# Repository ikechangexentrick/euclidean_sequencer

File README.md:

# euclidean_sequencer
Sequencer producing Euclidean rhythm

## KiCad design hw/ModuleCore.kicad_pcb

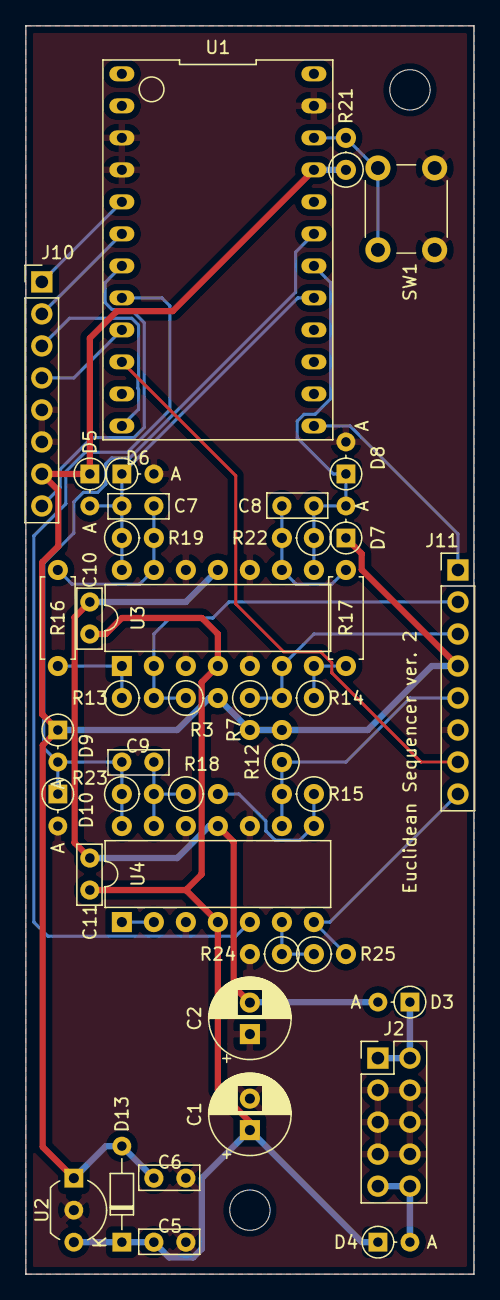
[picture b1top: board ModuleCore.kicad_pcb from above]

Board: 2 copper layers, 35.6 x 99.1 mm, 43 parts (0 on the bottom side), 30 nets.

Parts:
C1, C2: 100u; CP_Radial_D6.3mm_P2.50mm
C5, C6, C10, C11: 0.1u; C_Axial_L4.8mm_D2.0mm_P2.54mm_Horizontal
C7, C8, C9: 100p; C_Axial_L4.8mm_D2.0mm_P2.54mm_Horizontal
D3, D4: D_Schottky; D_DO-34_SOD68_P2.54mm_Vertical_AnodeUp
D5, D6, D7, D8, D9, D10: 1N4148; D_DO-34_SOD68_P2.54mm_Vertical_AnodeUp
D13: 1N4148; D_DO-34_SOD68_P7.62mm_Horizontal
J2: power_bus; PinHeader_2x05_P2.54mm_Vertical
J10: Conn_Left; PinHeader_1x08_P2.54mm_Vertical
J11: Conn_Right; PinHeader_1x08_P2.54mm_Vertical
R3, R7, R12, R13, R14, R15: 100k; R_Axial_DIN0207_L6.3mm_D2.5mm_P2.54mm_Vertical
R16, R17: 10k; R_Axial_DIN0207_L6.3mm_D2.5mm_P7.62mm_Horizontal
R18, R21: 10k; R_Axial_DIN0207_L6.3mm_D2.5mm_P2.54mm_Vertical
R19, R22, R23: 4.7k; R_Axial_DIN0207_L6.3mm_D2.5mm_P2.54mm_Vertical
R24: 820; R_Axial_DIN0207_L6.3mm_D2.5mm_P2.54mm_Vertical
R25: 1.5k; R_Axial_DIN0207_L6.3mm_D2.5mm_P2.54mm_Vertical
SW1: reset; SW_PUSH_6mm
U1: ProMicro; Pro_Micro_Top_side_Up
U2: LM78L05_TO92; TO-92_Inline_Wide
U3, U4: TL074; DIP-14_W7.62mm
e: MountingHole_3.2mm_M3
e#2: MountingHole_3.2mm_M3

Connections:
+5V: C6.1, D5.1, D7.1, D9.1, D13.2, J10.7, J11.4, R3.2, R7.2, R12.2, R21.1, U1.21, U2.1
+12V: C1.1, C5.1, C10.1, C11.1, D4.1, D13.1, U2.3, U3.4, U4.4
-12V: C2.2, C10.2, C11.2, D3.2, U3.11, U4.11
/_module_core/beat: U1.8, U4.5
/_module_core/beat_out: J11.8, R25.2, U4.7
/_module_core/btn_enter: J10.3, U1.12
/_module_core/clock: J11.7, U1.10
/_module_core/cv_len: C7.2, D5.2, D6.1, R19.1, U1.17, U3.14
/_module_core/cv_len_in: J11.2, R3.1, R13.2, U3.2
/_module_core/cv_num: C8.2, D7.2, D8.1, R22.1, U1.18, U3.8
/_module_core/cv_num_in: J11.3, R7.1, R14.2, U3.6
/_module_core/cv_select_in: J10.8, U1.7
/_module_core/cv_sft: C9.2, D9.2, D10.1, R23.1, U1.19, U4.14
/_module_core/cv_sft_in: J11.5, R12.1, R15.2, U4.9
/_module_core/rsw_1: J11.1, U1.13
/_module_core/rsw_2: J10.4, U1.9
/_module_core/scl: J10.2, U1.6
/_module_core/sda: J10.1, U1.5
GND: C1.2, C2.1, C5.2, C6.2, D6.2, D8.2, D10.2, J2.3, J2.4, J2.5, J2.6, J2.7, J2.8, J10.5, J10.6, J11.6, R24.2, SW1.2, U1.3, U1.4, U1.23, U2.2, U3.3, U3.5, U3.10, U3.12, U4.3, U4.10, U4.12
unnamed: C7.1, R16.1, R19.2, U3.13
unnamed: C8.1, R17.1, R22.2, U3.9
unnamed: C9.1, R18.1, R23.2, U4.13
unnamed: D3.1, J2.1, J2.2
unnamed: D4.2, J2.9, J2.10
unnamed: R13.1, R16.2, U3.1
unnamed: R14.1, R17.2, U3.7
unnamed: R15.1, R18.2, U4.8
unnamed: R21.2, SW1.1, U1.22
unnamed: R24.1, R25.1, U4.6
unnamed: U4.1, U4.2

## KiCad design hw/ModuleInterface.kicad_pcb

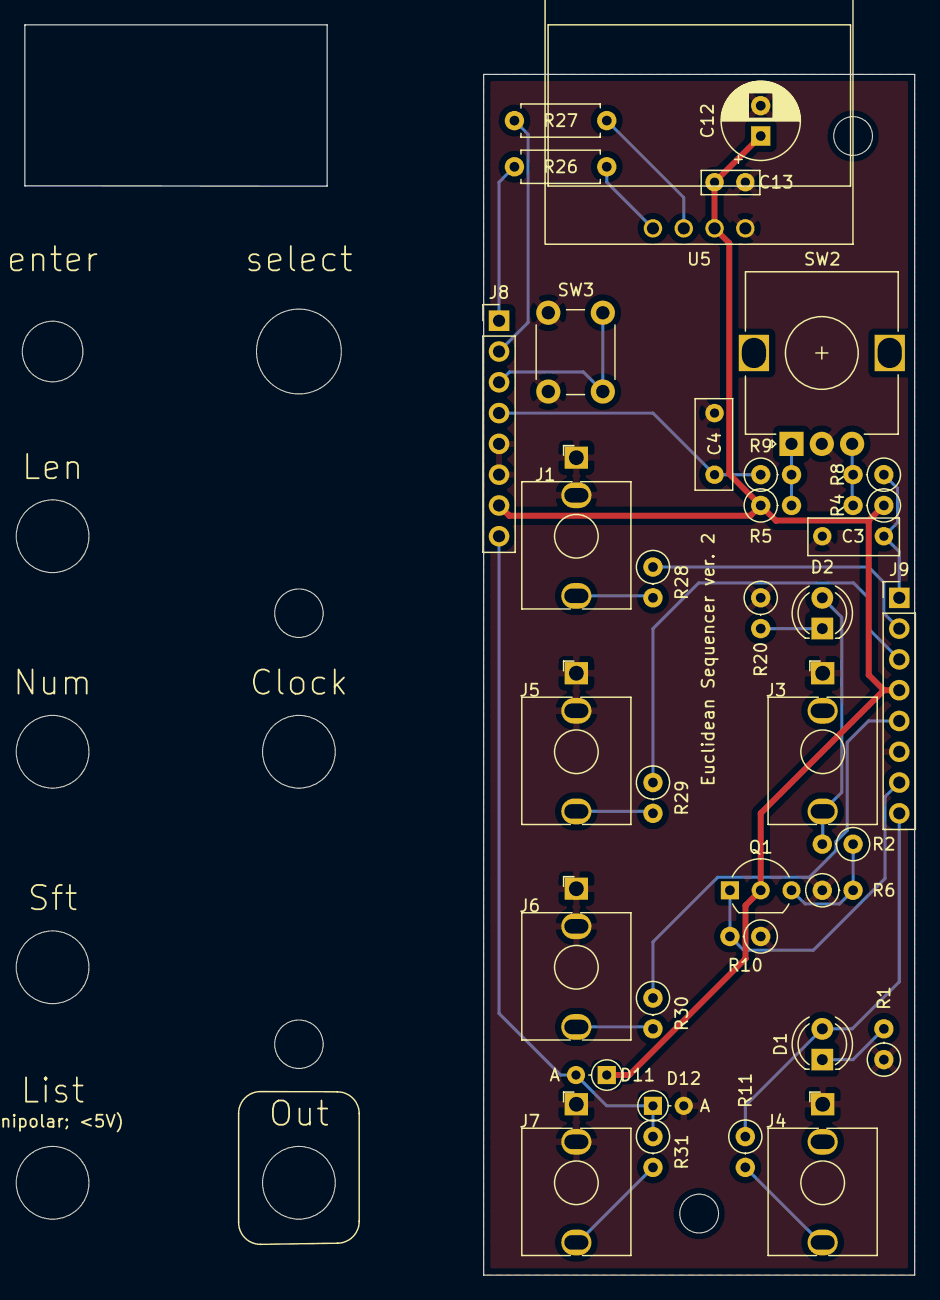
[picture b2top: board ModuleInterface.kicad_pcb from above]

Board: 2 copper layers, 73.4 x 103.1 mm, 44 parts (0 on the bottom side), 26 nets.

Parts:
C3, C4: 0.1u; C_Axial_L4.8mm_D3.1mm_P5.08mm_Horizontal
C12: 100u; CP_Radial_D6.3mm_P2.50mm
C13: 0.1u; C_Axial_L4.8mm_D2.0mm_P2.54mm_Horizontal
Clock: annotation_3.5mm_jack_in
D1: led_beat; LED_D4.0mm
D2: led_clock; LED_D4.0mm
D11, D12: 1N4148; D_DO-34_SOD68_P2.54mm_Vertical_AnodeUp
J1: CV_len; mono_jack_3.5mm
J3: clock_in; mono_jack_3.5mm
J4: beat_out; mono_jack_3.5mm
J5: CV_num; mono_jack_3.5mm
J6: CV_sft; mono_jack_3.5mm
J7: CV_select; mono_jack_3.5mm
J8: Conn_Left; PinHeader_1x08_P2.54mm_Vertical
J9: Conn_Right; PinHeader_1x08_P2.54mm_Vertical
Len: annotation_3.5mm_jack_in
List: annotation_3.5mm_jack_in
Num: annotation_3.5mm_jack_in
Out: annotation_3.5mm_jack_out
Q1: 2SC1815; TO-92_Inline_Wide
R1, R4, R5, R8, R9, R20: 10k; R_Axial_DIN0207_L6.3mm_D2.5mm_P2.54mm_Vertical
R2, R6, R10, R28, R29, R30, R31: 100k; R_Axial_DIN0207_L6.3mm_D2.5mm_P2.54mm_Vertical
R11: 1k; R_Axial_DIN0207_L6.3mm_D2.5mm_P2.54mm_Vertical
R26, R27: 1k; R_Axial_DIN0207_L6.3mm_D2.5mm_P7.62mm_Horizontal
SW2: Rotary_Encoder; RotaryEncoder_Alps_EC12E_Vertical_H20mm
SW3: enter; SW_PUSH_6mm
Sft: annotation_3.5mm_jack_in
U5: OLED_Display_SSD1306; aki_OLED_0.96in
enter: MountingHole_5mm
select: annotation_7mm

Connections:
+5V: C12.1, C13.2, D11.1, J8.7, J9.4, Q1.2, R4.1, R5.1, U5.2
/_module_interface/beat_out: D1.2, J9.8, R11.1
/_module_interface/btn_enter: J8.3, SW3.2
/_module_interface/clock: J9.7, Q1.1, R10.2
/_module_interface/cv_len_in: J9.2, R28.1
/_module_interface/cv_num_in: J9.3, R29.1
/_module_interface/cv_select_in: D11.2, D12.1, J8.8, R31.1
/_module_interface/cv_sft_in: J9.5, R30.1
/_module_interface/rsw_1: C3.1, J9.1, R8.1
/_module_interface/rsw_2: C4.1, J8.4, R9.1
/_module_interface/scl: J8.2, R27.1
/_module_interface/sda: J8.1, R26.1
GND: C3.2, C4.2, C12.2, C13.1, D12.2, J1.S, J1.TN, J3.S, J4.S, J5.S, J5.TN, J6.S, J6.TN, J7.S, J7.TN, J8.5, J8.6, J9.6, R1.1, R6.1, R10.1, R20.1, SW2.C, SW3.1, U5.1
unnamed: D1.1, R1.2
unnamed: D2.1, R20.2
unnamed: D2.2, J3.T, R2.2
unnamed: J1.T, R28.2
unnamed: J4.T, R11.2
unnamed: J5.T, R29.2
unnamed: J6.T, R30.2
unnamed: J7.T, R31.2
unnamed: Q1.3, R2.1, R6.2
unnamed: R4.2, R8.2, SW2.B
unnamed: R5.2, R9.2, SW2.A
unnamed: R26.2, U5.4
unnamed: R27.2, U5.3

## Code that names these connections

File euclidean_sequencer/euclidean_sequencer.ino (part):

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//  -----------------------------------------------

//static const int PIN_RANDOM_SEED = 21; // A3
static const int PIN_CV_SFT = 20; // A2
static const int PIN_CV_NUM = 19; // A1
static const int PIN_CV_LEN = 18; // A0
static const int PIN_CV_SELECT = 21; // A3

static const int PIN_ROTARY_SW1 = 10; // pin change interrupt
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
	//randomSeed(analogRead(PIN_RANDOM_SEED));

	pinMode(PIN_CV_LEN, INPUT);
	pinMode(PIN_CV_NUM, INPUT);
	pinMode(PIN_CV_SFT, INPUT);
	pinMode(PIN_CV_SELECT, INPUT);

	pinMode(PIN_ROTARY_SW1, INPUT);
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	auto t_cur = millis();

/*
	auto a0 = analogRead(PIN_CV_LEN);
	char buf[8];
	snprintf(buf, 8, "%4d", a0);
	serial_log("a0= %4d", a0);
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
	if (t_cur-t_prev_disp > 20) {
		app->set_cv(
			analogRead(PIN_CV_LEN),
			analogRead(PIN_CV_NUM),
			analogRead(PIN_CV_SFT),
			analogRead(PIN_CV_SELECT)
		);

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
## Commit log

2022-09-08 Euclidean Sequencer, ver. 2
2022-09-08 Adjusted to run on pro micro. appended "shift" function.
2022-09-08 sequencer that emits Euclidean rhythms of length of 16.
2022-09-08 Button, rotary encoder, and subclasses are moved to library/button.
    7-segment display is now supported.
    At the first beat, decimal point is on.
2022-09-08 Fixed a bug.
2022-09-19 worked on the PCB. - adjusted CV scale parameters - removed debug code
2022-09-27 Adjusted an initial setting.
